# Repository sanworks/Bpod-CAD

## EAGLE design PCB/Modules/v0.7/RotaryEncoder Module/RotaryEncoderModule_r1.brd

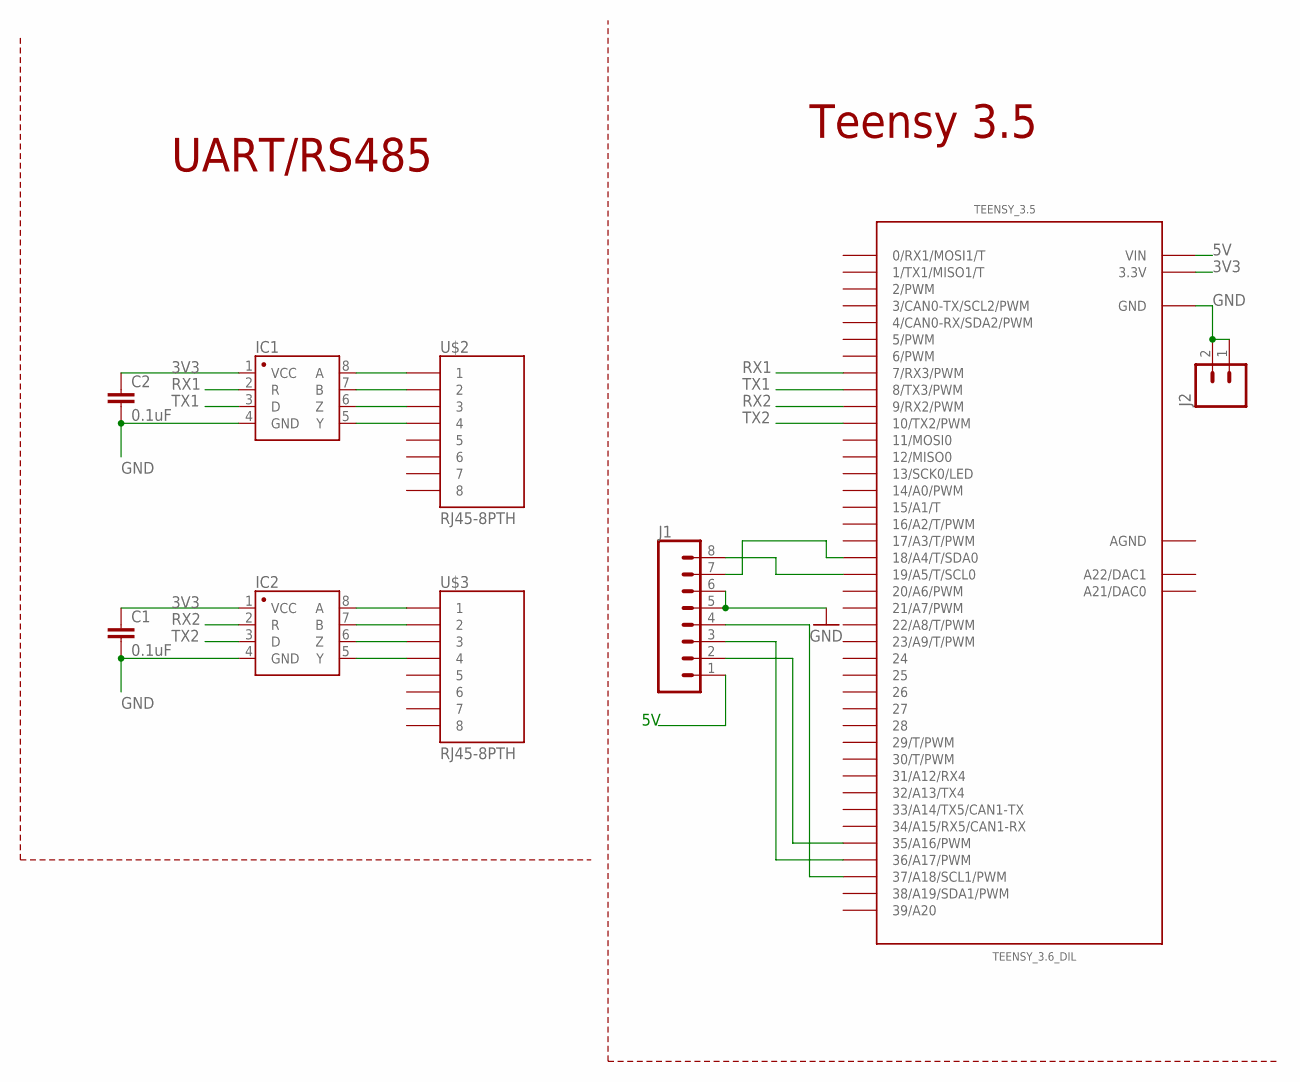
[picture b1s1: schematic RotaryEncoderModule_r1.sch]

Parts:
C1, C2: 0.1uF; 1206
IC1, IC2: SN65HVD31DR; SO08
J1: CONN_083.5MM-8; SCREWTERMINAL-3.5MM-8
J2: M023.5MM; SCREWTERMINAL-3.5MM-2
TEENSY_3.5: TEENSY_3.6_DIL
U$2, U$3: RJ45-8PTH; RJ45-8

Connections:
3V3: C1.1, C2.1, IC1.1 (VCC), IC2.1 (VCC), TEENSY_3.5.3.3V, TEENSY_3.5.3.3V3 (3.3V)
5V: J1.1, TEENSY_3.5.VIN
AGND: TEENSY_3.5.AGND
GND: C1.2, C2.2, IC1.4 (GND), IC2.4 (GND), J1.5, J1.6, J2.1, J2.2, TEENSY_3.5.GND, TEENSY_3.5.GND1 (GND)
unnamed: IC1.6 (Z), U$2.3
unnamed: IC1.8 (A), U$2.1
unnamed: IC1.5 (Y), U$2.4
unnamed: IC1.7 (B), U$2.2
unnamed: IC2.6 (Z), U$3.3
unnamed: IC2.5 (Y), U$3.4
unnamed: IC2.8 (A), U$3.1
unnamed: IC2.7 (B), U$3.2
unnamed: J1.8, TEENSY_3.5.19/A5 (19/A5/T/SCL0)
unnamed: J1.7, TEENSY_3.5.18/A4 (18/A4/T/SDA0)
unnamed: J1.2, TEENSY_3.5.35/A16 (35/A16/PWM)
unnamed: J1.3, TEENSY_3.5.36/A17 (36/A17/PWM)
unnamed: J1.4, TEENSY_3.5.37/A18 (37/A18/SCL1/PWM)
RX1: IC1.2 (R), TEENSY_3.5.7 (7/RX3/PWM)
RX2: IC2.2 (R), TEENSY_3.5.9 (9/RX2/PWM)
TX1: IC1.3 (D), TEENSY_3.5.8 (8/TX3/PWM)
TX2: IC2.3 (D), TEENSY_3.5.10 (10/TX2/PWM)

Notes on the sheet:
Teensy 3.5
UART/RS485

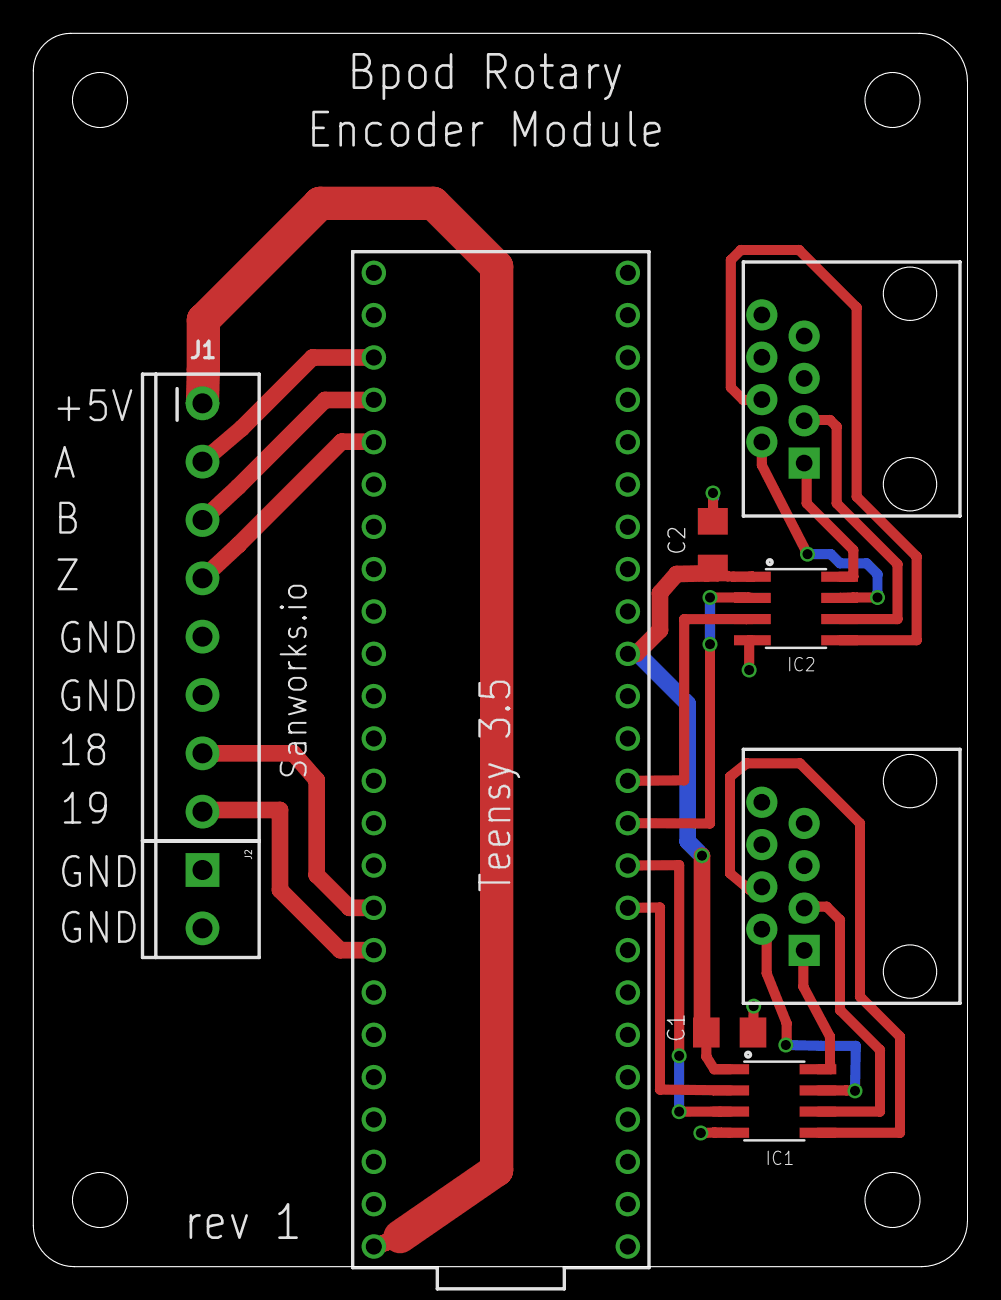
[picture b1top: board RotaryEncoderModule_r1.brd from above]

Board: 2 copper layers, 56.0 x 74.0 mm, 13 parts (0 on the bottom side), 20 nets.

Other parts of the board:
U$5, U$6, U$7, U$8: STAND-OFF

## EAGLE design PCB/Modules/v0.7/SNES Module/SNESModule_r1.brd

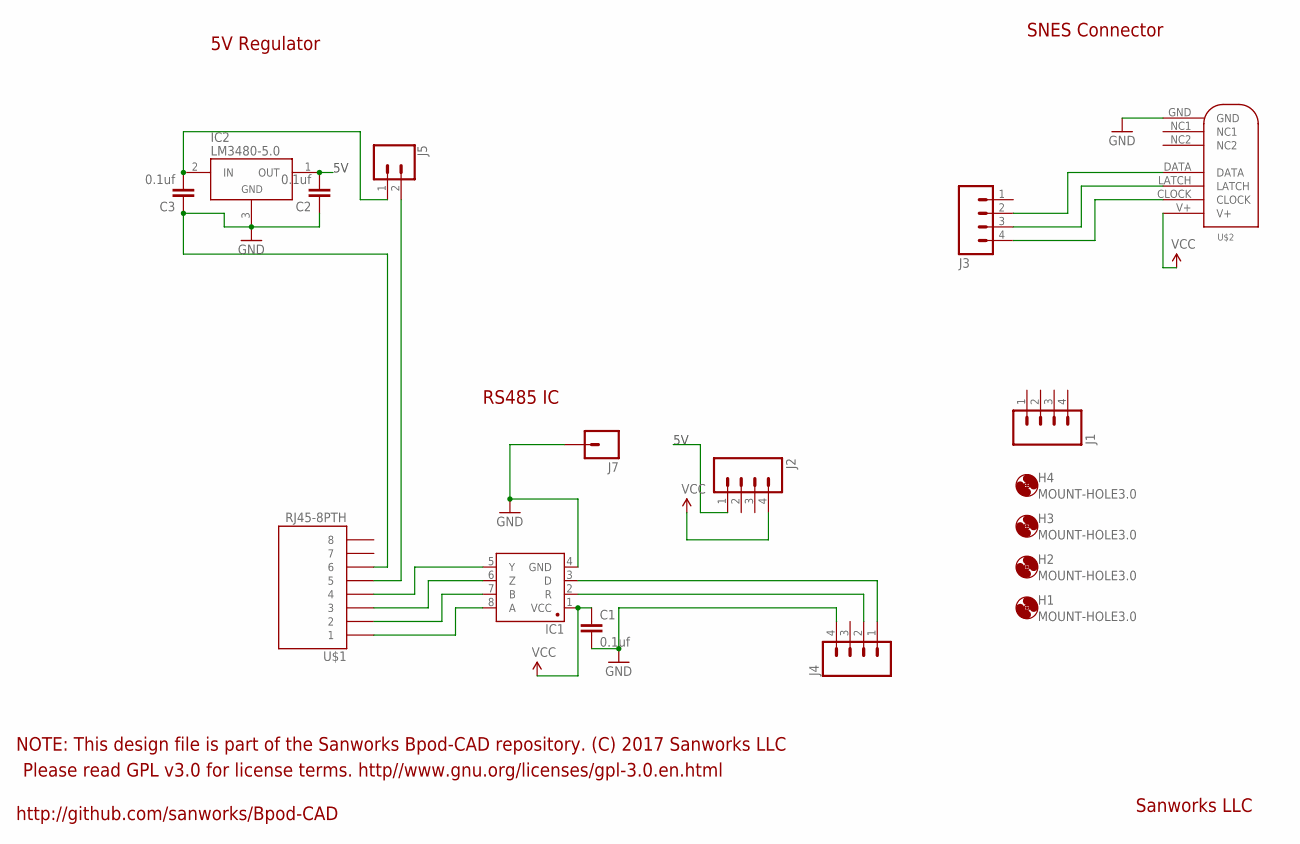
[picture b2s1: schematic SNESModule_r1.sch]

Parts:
C1, C2, C3: 0.1uf; 1206
H1, H2, H3, H4: MOUNT-HOLE3.0; 3,0
IC1: SN65HVD31DR; SO08
IC2: LM3480-5.0; SOT-23-3
J1, J2, J3, J4: M04PTH; 1X04
J5: CONN_02; 1X02
J7: M01PTH; 1X01
U$1: RJ45-8PTH; RJ45-8
U$2: SNES_CONNECTOR

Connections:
5V: C2.2, IC2.1 (OUT), J2.1
GND: C1.2, C2.1, C3.1, IC1.4 (GND), IC2.3 (GND), J4.4, J7.1, U$1.6, U$2.GND
unnamed: J3.2, U$2.DATA
unnamed: J3.3, U$2.LATCH
unnamed: J3.4, U$2.CLOCK
unnamed: IC1.3 (D), J4.1
unnamed: IC1.2 (R), J4.2
unnamed: IC1.8 (A), U$1.1
unnamed: IC1.7 (B), U$1.2
unnamed: IC1.6 (Z), U$1.3
unnamed: IC1.5 (Y), U$1.4
unnamed: J5.2, U$1.5
unnamed: C3.2, IC2.2 (IN), J5.1
VCC: C1.1, IC1.1 (VCC), J2.4, U$2.V+

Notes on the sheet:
Please read GPL v3.0 for license terms. http//www.gnu.org/licenses/gpl-3.0.en.html
NOTE: This design file is part of the Sanworks Bpod-CAD repository. (C) 2017 Sanworks LLC
http://github.com/sanworks/Bpod-CAD
Sanworks LLC
SNES Connector
5V Regulator
RS485 IC

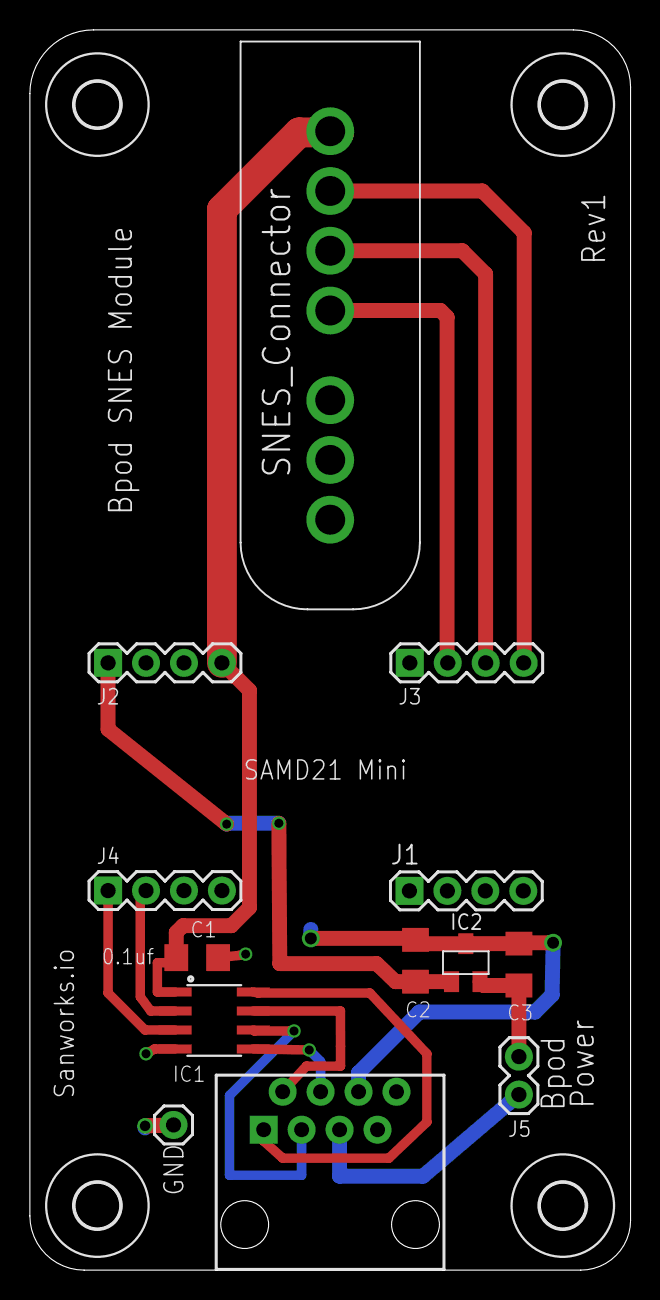
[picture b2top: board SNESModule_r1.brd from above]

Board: 2 copper layers, 40.2 x 83.0 mm, 17 parts (0 on the bottom side), 14 nets.

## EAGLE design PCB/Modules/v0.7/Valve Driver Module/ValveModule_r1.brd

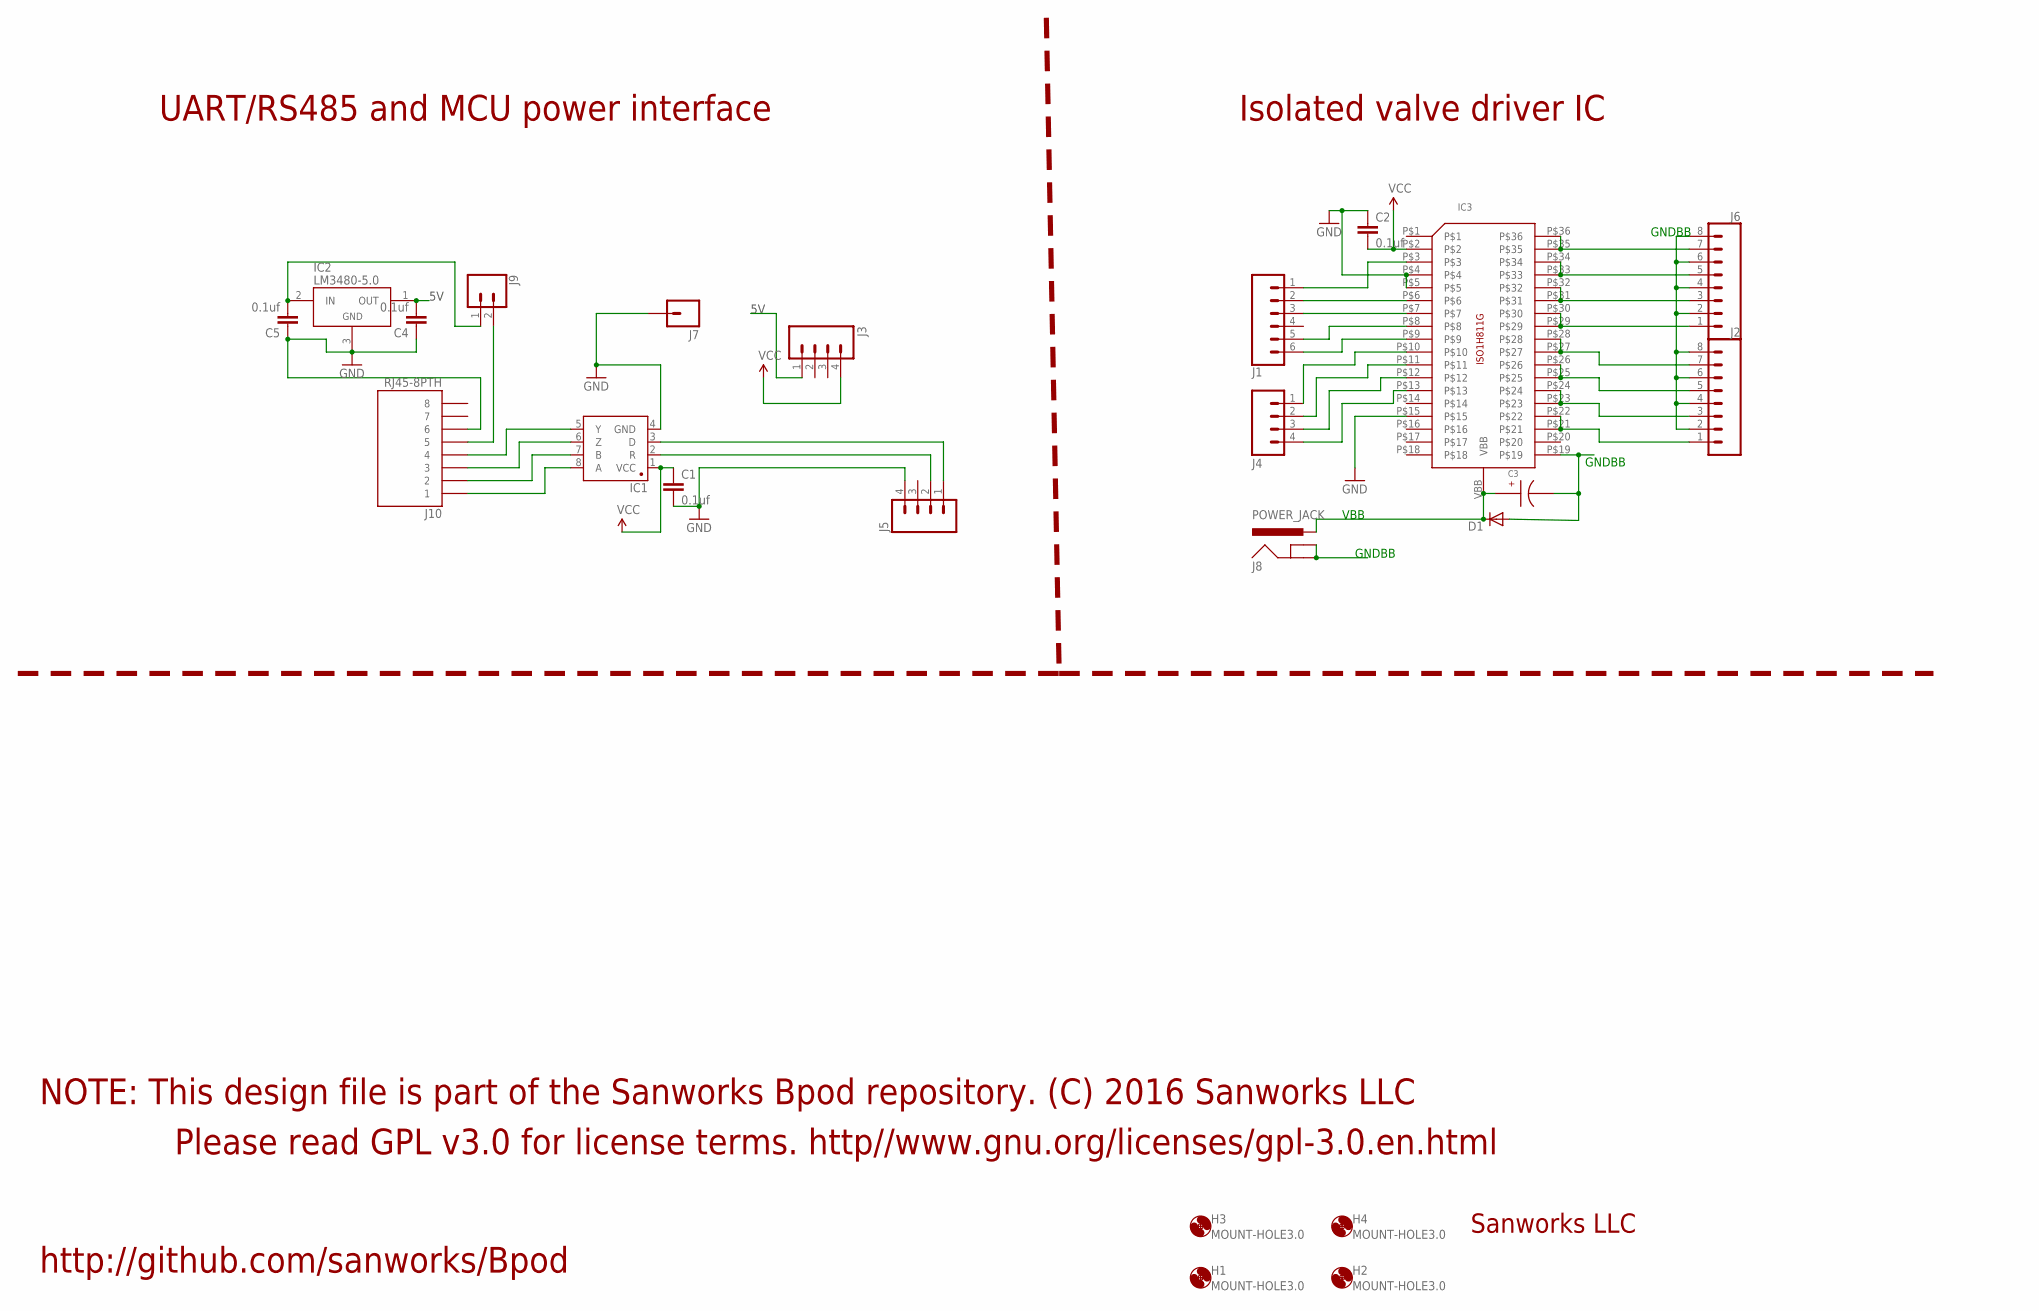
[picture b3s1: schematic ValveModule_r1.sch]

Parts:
C1, C2, C4, C5: 0.1uf; 1206
C3: EEE-FK1H100UR
D1: DIODE-DO214AA; DO214AA
H1, H2, H3, H4: MOUNT-HOLE3.0; 3,0
IC1: SN65HVD31DR; SO08
IC2: LM3480-5.0; SOT-23-3
IC3: ISO1H811G
J1: CONN_06SILK_FEMALE_PTH; 1X06
J2, J6: CONN_083.5MM-8; SCREWTERMINAL-3.5MM-8
J3, J4, J5: M04PTH; 1X04
J7: M01PTH; 1X01
J8: POWER_JACK; POWER_JACK_PTH
J9: CONN_02; 1X02
J10: RJ45-8PTH; RJ45-8

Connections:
5V: C4.2, IC2.1 (OUT), J3.1
GND: C1.2, C2.1, C4.1, C5.1, IC1.4 (GND), IC2.3 (GND), IC3.P$4, IC3.P$5, IC3.P$15, J5.4, J7.1, J10.6
GNDBB: C3.CATHODE, D1.A, IC3.P$19, J2.2, J2.4, J2.6, J2.8, J6.2, J6.4, J6.6, J6.8, J8.GND, J8.GNDBREAK
unnamed: IC3.P$35, IC3.P$36, J6.7
unnamed: IC3.P$3, J1.1
unnamed: IC3.P$6, J1.2
unnamed: IC1.3 (D), J5.1
unnamed: IC3.P$7, J1.3
unnamed: IC1.2 (R), J5.2
unnamed: IC1.8 (A), J10.1
unnamed: IC1.7 (B), J10.2
unnamed: IC1.6 (Z), J10.3
unnamed: IC1.5 (Y), J10.4
unnamed: IC3.P$8, J1.5
unnamed: IC3.P$9, J1.6
unnamed: IC3.P$10, J4.1
unnamed: IC3.P$11, J4.2
unnamed: IC3.P$12, J4.3
unnamed: IC3.P$13, J4.4
unnamed: IC3.P$33, IC3.P$34, J6.5
unnamed: IC3.P$31, IC3.P$32, J6.3
unnamed: IC3.P$29, IC3.P$30, J6.1
unnamed: IC3.P$27, IC3.P$28, J2.7
unnamed: IC3.P$25, IC3.P$26, J2.5
unnamed: IC3.P$23, IC3.P$24, J2.3
unnamed: IC3.P$21, IC3.P$22, J2.1
unnamed: J9.2, J10.5
unnamed: C5.2, IC2.2 (IN), J9.1
VBB: C3.ANODE, D1.C, IC3.VBB, J8.PWR
VCC: C1.1, C2.2, IC1.1 (VCC), IC3.P$2, J3.4

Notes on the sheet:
VBB
GNDBB
UART/RS485 and MCU power interface
Isolated valve driver IC
Please read GPL v3.0 for license terms. http//www.gnu.org/licenses/gpl-3.0.en.html
NOTE: This design file is part of the Sanworks Bpod repository. (C) 2016 Sanworks LLC
Sanworks LLC
http://github.com/sanworks/Bpod

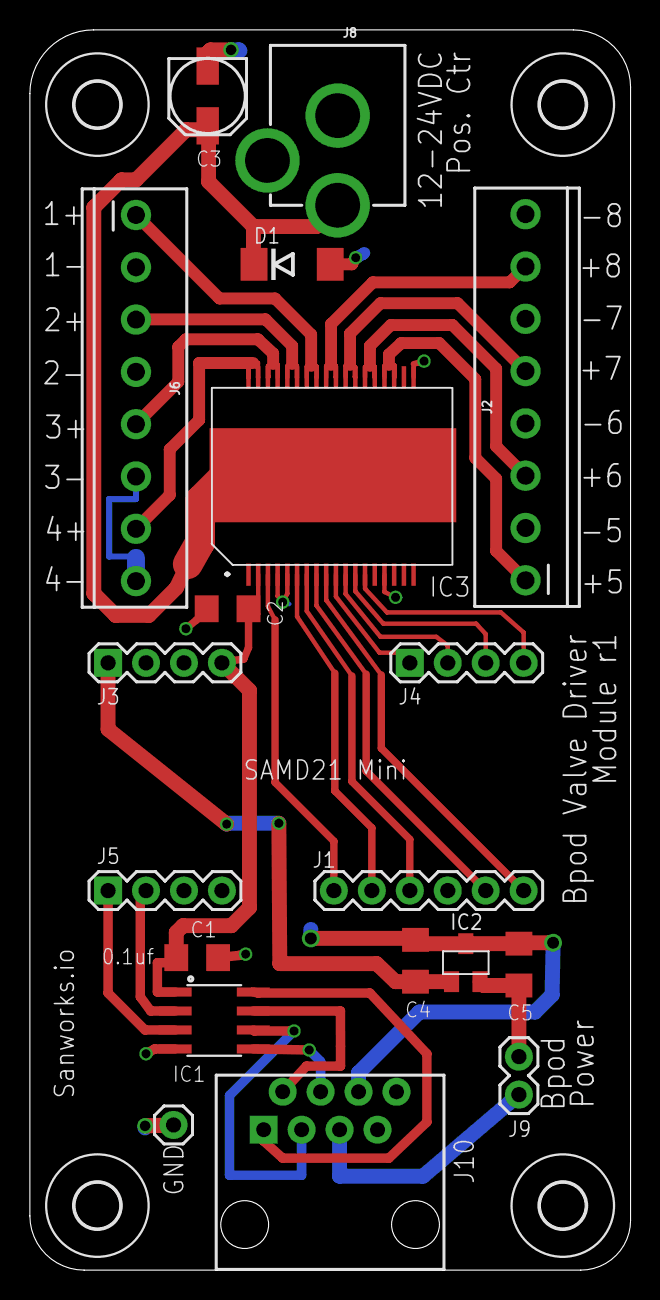
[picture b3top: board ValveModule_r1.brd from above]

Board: 2 copper layers, 40.2 x 83.0 mm, 23 parts (0 on the bottom side), 30 nets.

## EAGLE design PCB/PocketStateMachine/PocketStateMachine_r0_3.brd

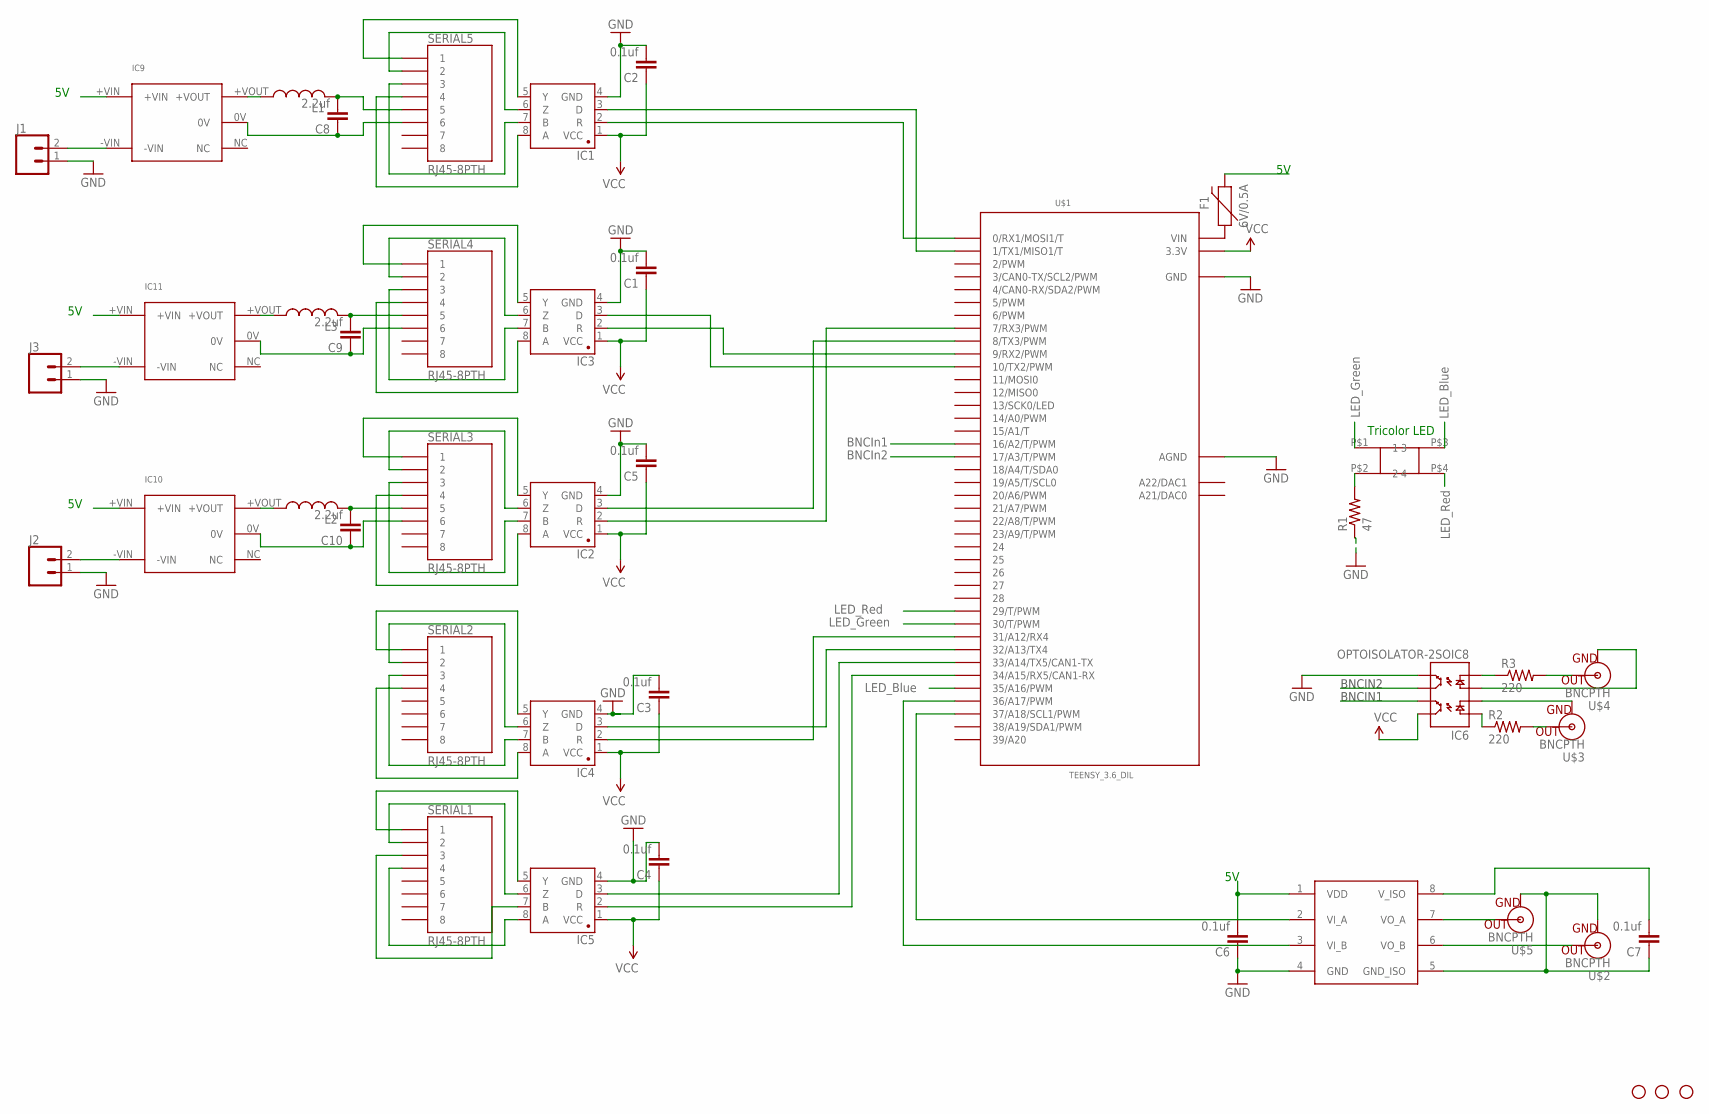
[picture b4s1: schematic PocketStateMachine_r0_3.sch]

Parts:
C1, C2, C3, C4, C5, C6, C7: 0.1uf; 1206
C8, C9, C10: 2.2uf; 1206
F1: 6V/0.5A; 1206
IC1, IC2, IC3, IC4, IC5: SN65HVD31DR; SO08
IC6: OPTOISOLATOR-2SOIC8; SO08-2
IC7: ADUM5240; SO08
IC9, IC10, IC11: MTU1D0505MC
J1, J2, J3: CONN_02; 1X02
JP3, JP4, JP5: STAND-OFF
L1, L2, L3: L-USL3225M; L3225M
R1: 47; 1206
R2, R3: 220; 1206
SERIAL1, SERIAL2, SERIAL3, SERIAL4, SERIAL5: RJ45-8PTH; RJ45-8
U$1: TEENSY_3.6_DIL
U$2, U$3, U$4, U$5: BNCPTH; BNC
U$8: SQUARE_TRICOLOR_LED

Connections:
5V: C6.2, F1.2, IC7.1 (VDD), IC9.+VIN, IC10.+VIN, IC11.+VIN
BNCIN1: IC6.7 (EM1), U$1.16/A2 (16/A2/T/PWM)
BNCIN2: IC6.6 (CL2), U$1.17/A3 (17/A3/T/PWM)
GND: C1.2, C2.2, C3.2, C4.2, C5.2, C6.1, IC1.4 (GND), IC2.4 (GND), IC3.4 (GND), IC4.4 (GND), IC5.4 (GND), IC6.5 (EM2), IC7.4 (GND), J1.1, J2.1, J3.1, R1.1, U$1.AGND, U$1.GND, U$1.GND1 (GND)
ISOGND: C7.1, IC7.5 (GND_ISO), U$2.GND, U$5.GND
LED_BLUE: U$1.35/A16 (35/A16/PWM), U$8.P$3 (3)
LED_GREEN: U$1.30 (30/T/PWM), U$8.P$1 (1)
LED_RED: U$1.29 (29/T/PWM), U$8.P$4 (4)
unnamed: IC3.8 (A), SERIAL4.4
unnamed: IC3.7 (B), SERIAL4.3
unnamed: IC3.6 (Z), SERIAL4.2
unnamed: IC3.5 (Y), SERIAL4.1
unnamed: IC3.2 (R), U$1.9 (9/RX2/PWM)
unnamed: IC3.3 (D), U$1.10 (10/TX2/PWM)
unnamed: IC1.8 (A), SERIAL5.4
unnamed: IC1.7 (B), SERIAL5.3
unnamed: IC1.6 (Z), SERIAL5.2
unnamed: IC1.5 (Y), SERIAL5.1
unnamed: IC1.2 (R), U$1.0 (0/RX1/MOSI1/T)
unnamed: IC1.3 (D), U$1.1 (1/TX1/MISO1/T)
unnamed: IC6.3 (A2), U$4.GND
unnamed: R3.2, U$4.S (OUT)
unnamed: R2.2, U$3.S (OUT)
unnamed: IC6.2 (C1), U$3.GND
unnamed: IC2.8 (A), SERIAL3.4
unnamed: IC2.7 (B), SERIAL3.3
unnamed: IC2.6 (Z), SERIAL3.2
unnamed: IC7.3 (VI_B), U$1.36/A17 (36/A17/PWM)
unnamed: IC2.5 (Y), SERIAL3.1
unnamed: IC2.2 (R), U$1.7 (7/RX3/PWM)
unnamed: C8.2, L1.2, SERIAL5.5
unnamed: IC7.2 (VI_A), U$1.37/A18 (37/A18/SCL1/PWM)
unnamed: R1.2, U$8.P$2 (2)
unnamed: C8.1, IC9.0V, SERIAL5.6
unnamed: IC7.7 (VO_A), U$5.S (OUT)
unnamed: IC2.3 (D), U$1.8 (8/TX3/PWM)
unnamed: F1.1, U$1.VIN
unnamed: IC7.6 (VO_B), U$2.S (OUT)
unnamed: IC5.8 (A), SERIAL1.4
unnamed: IC5.7 (B), SERIAL1.3
unnamed: IC5.6 (Z), SERIAL1.2
unnamed: IC5.5 (Y), SERIAL1.1
unnamed: IC4.8 (A), SERIAL2.4
unnamed: IC4.7 (B), SERIAL2.3
unnamed: IC4.6 (Z), SERIAL2.2
unnamed: IC9.+VOUT, L1.1
unnamed: IC4.5 (Y), SERIAL2.1
unnamed: IC9.-VIN, J1.2
unnamed: IC5.2 (R), U$1.34/A15 (34/A15/RX5/CAN1-RX)
unnamed: C10.1, IC10.0V, SERIAL3.6
unnamed: C10.2, L2.2, SERIAL3.5
unnamed: IC10.+VOUT, L2.1
unnamed: IC10.-VIN, J2.2
unnamed: C9.1, IC11.0V, SERIAL4.6
unnamed: IC5.3 (D), U$1.33/A14 (33/A14/TX5/CAN1-TX)
unnamed: C9.2, L3.2, SERIAL4.5
unnamed: IC11.+VOUT, L3.1
unnamed: IC11.-VIN, J3.2
unnamed: IC4.2 (R), U$1.31/A12 (31/A12/RX4)
unnamed: IC4.3 (D), U$1.32/A13 (32/A13/TX4)
unnamed: IC6.1 (A1), R2.1
unnamed: IC6.4 (C2), R3.1
unnamed: C7.2, IC7.8 (V_ISO)
VCC: C1.1, C2.1, C3.1, C4.1, C5.1, IC1.1 (VCC), IC2.1 (VCC), IC3.1 (VCC), IC4.1 (VCC), IC5.1 (VCC), IC6.8 (CL1), U$1.3.3V, U$1.3.3V3 (3.3V)

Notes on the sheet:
Tricolor LED
LED_Blue
LED_Red
LED_Green
BNCIN1
BNCIN2
BNCIn1
BNCIn2

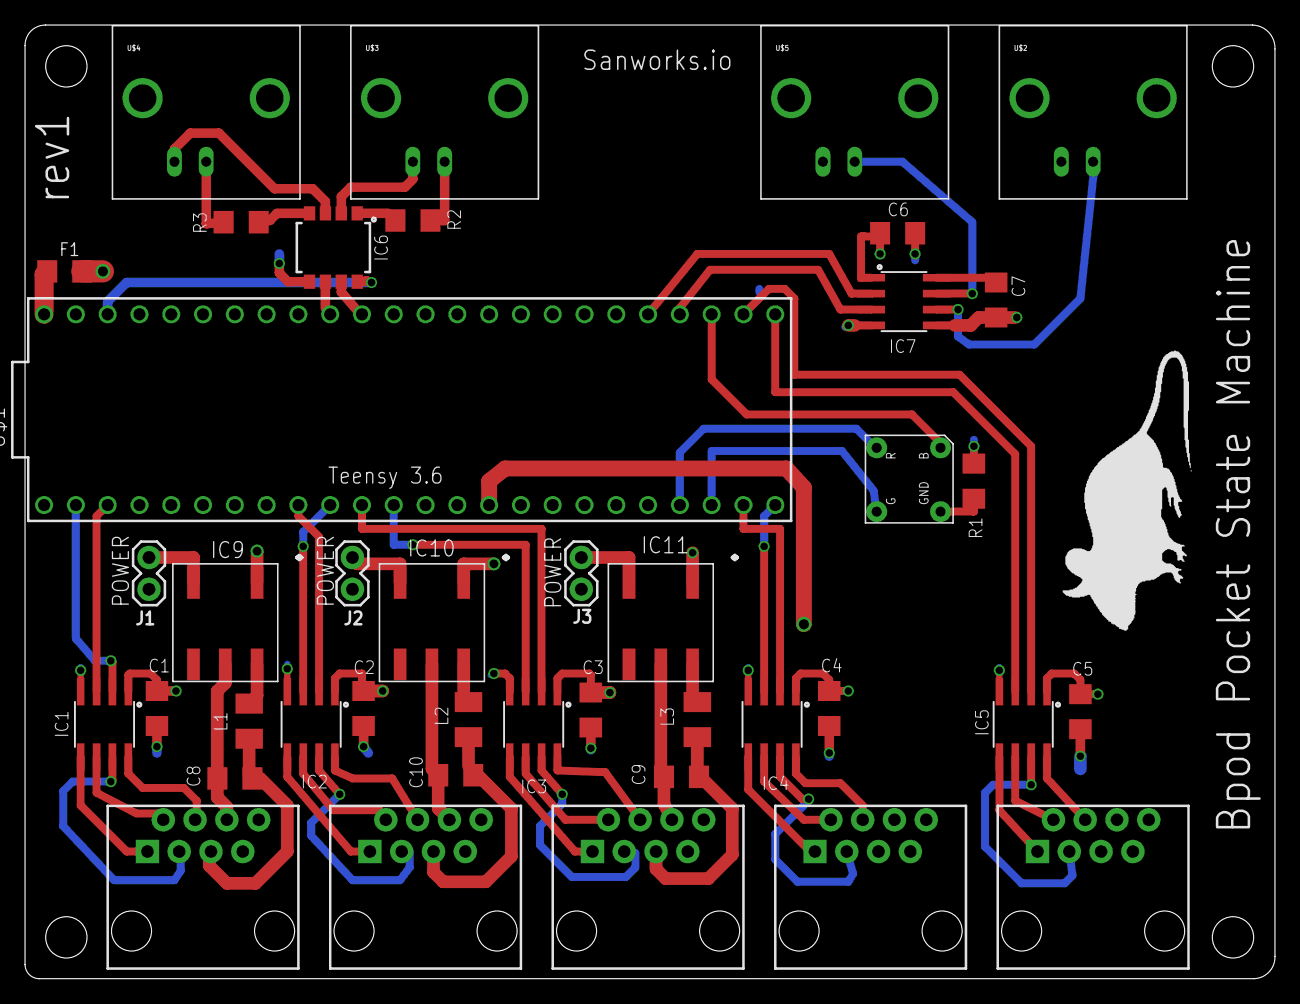
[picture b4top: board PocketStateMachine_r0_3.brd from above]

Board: 4 copper layers, 99.9 x 76.2 mm, 46 parts (0 on the bottom side), 64 nets.

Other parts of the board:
JP1: STAND-OFF
U$9: MOUSELOGO

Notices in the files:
parts and their libraries:
SparkFun-Capacitors: Licensing: Creative Commons ShareAlike 4.0 International - https://creativecommons.org/licenses/by-sa/4.0
SparkFun: Licensing: CC v3.0 Share-Alike You are welcome to use this library for commercial purposes.
